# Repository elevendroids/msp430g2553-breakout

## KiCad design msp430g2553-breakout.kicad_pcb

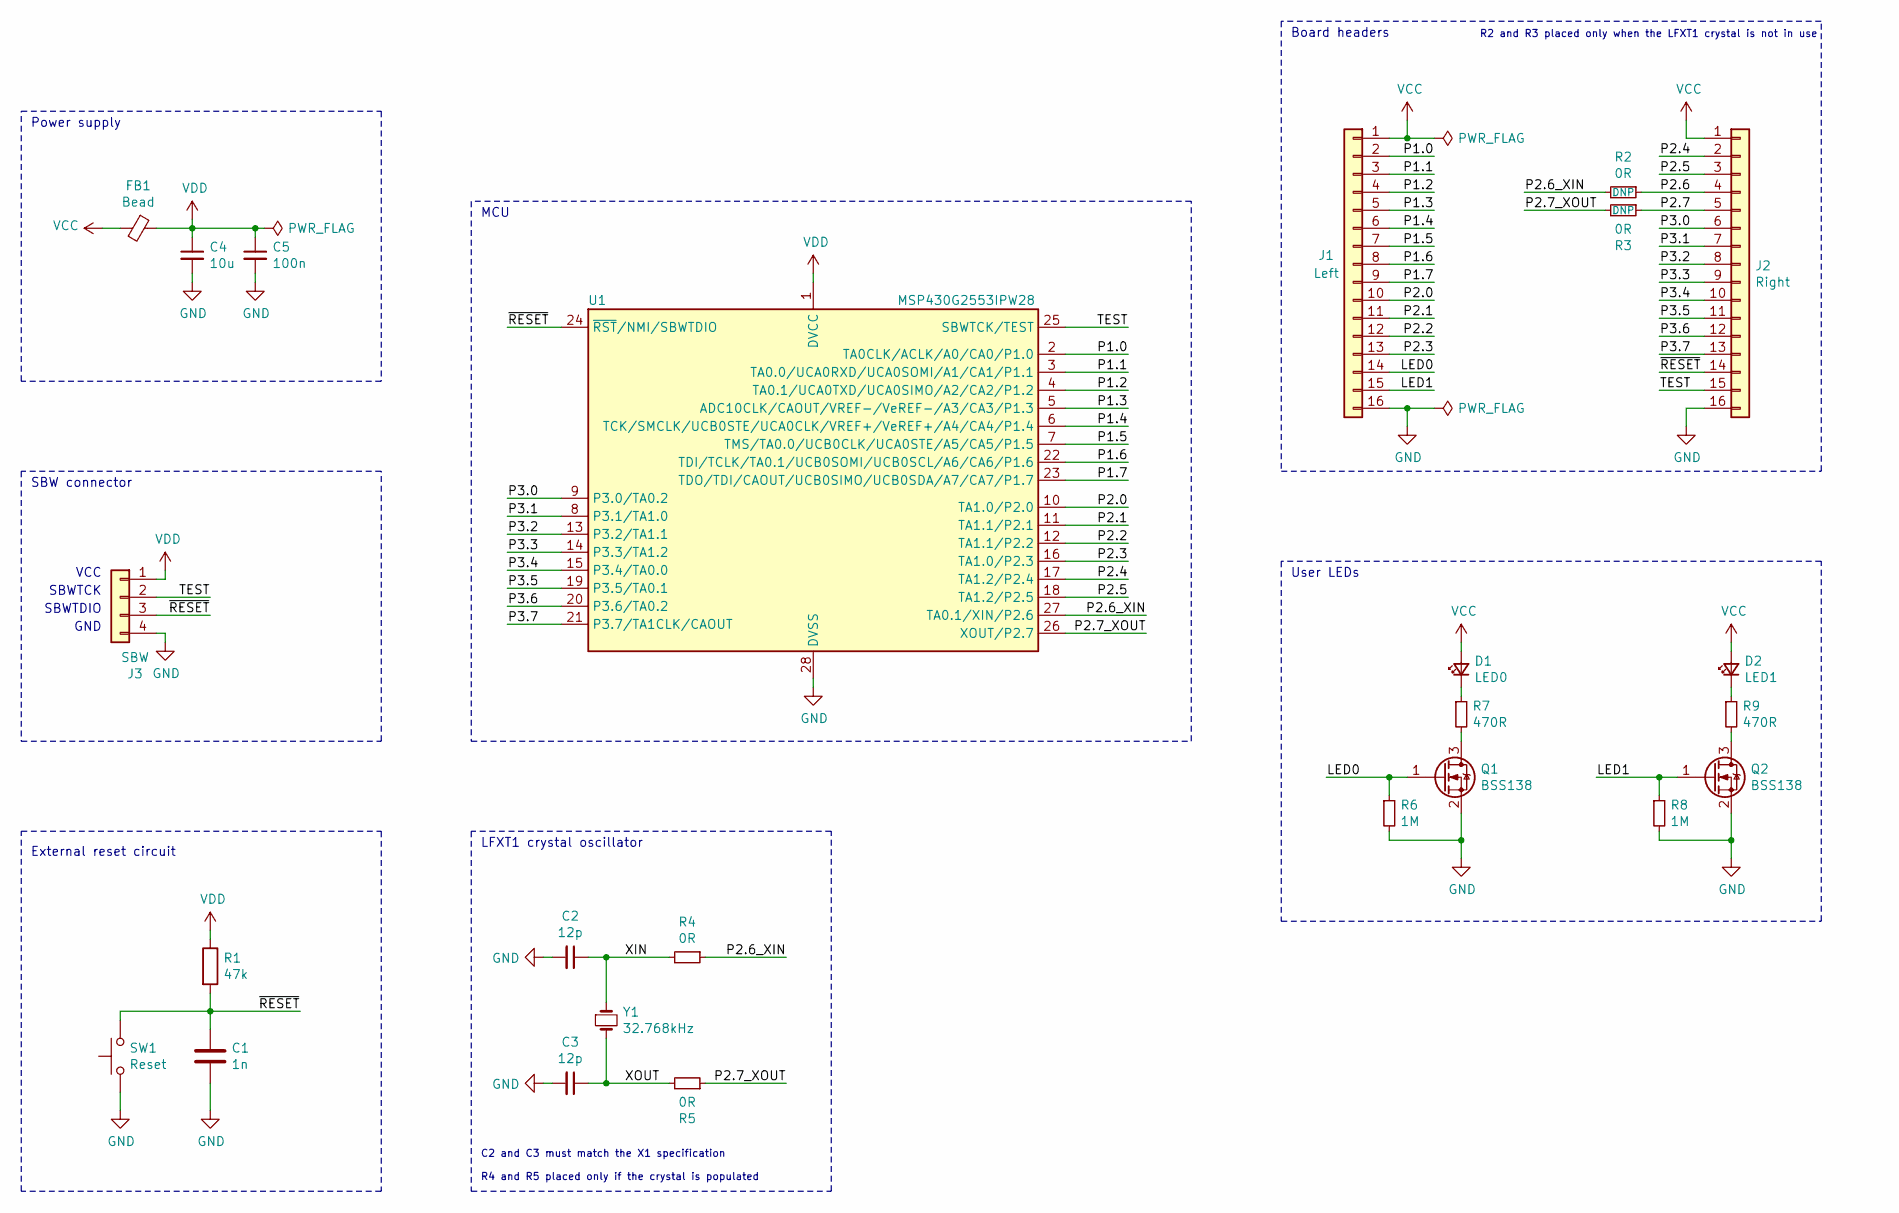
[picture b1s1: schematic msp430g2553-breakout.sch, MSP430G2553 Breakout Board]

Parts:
C1: 1n; C_0603_1608Metric
C2, C3: 12p; C_0603_1608Metric
C4: 10u; C_0805_2012Metric
C5: 100n; C_0603_1608Metric
D1: LED0; LED_0805_2012Metric
D2: LED1; LED_0805_2012Metric
FB1: Bead; L_0603_1608Metric
J1: Left; PinHeader_1x16_P2.54mm_Vertical
J2: Right; PinHeader_1x16_P2.54mm_Vertical
J3: SBW; PinHeader_1x04_P2.00mm_Vertical
Q1, Q2: BSS138; SOT-23
R1: 47k; R_0603_1608Metric
R2, R3, R4, R5: 0R; R_0402_1005Metric
R6, R8: 1M; R_0603_1608Metric
R7, R9: 470R; R_0603_1608Metric
SW1: Reset; SW_SPST_CK_RS282G05A3
U1: MSP430G2553IPW28; TSSOP-28_4.4x9.7mm_P0.65mm
Y1: 32.768kHz; Crystal_SMD_3215-2Pin_3.2x1.5mm

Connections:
/LED0: J1.14, Q1.1 (G), R6.1
/LED1: J1.15, Q2.1 (G), R8.1
/P1.0: J1.2, U1.2 (TA0CLK/ACLK/A0/CA0/P1.0)
/P1.1: J1.3, U1.3 (TA0.0/UCA0RXD/UCA0SOMI/A1/CA1/P1.1)
/P1.2: J1.4, U1.4 (TA0.1/UCA0TXD/UCA0SIMO/A2/CA2/P1.2)
/P1.3: J1.5, U1.5 (ADC10CLK/CAOUT/VREF-/VeREF-/A3/CA3/P1.3)
/P1.4: J1.6, U1.6 (TCK/SMCLK/UCB0STE/UCA0CLK/VREF+/VeREF+/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)
/P1.5: J1.7, U1.7 (TMS/TA0.0/UCB0CLK/UCA0STE/A5/CA5/P1.5)
/P1.6: J1.8, U1.22 (TDI/TCLK/TA0.1/UCB0SOMI/UCB0SCL/A6/CA6/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)
/P1.7: J1.9, U1.23 (TDO/TDI/CAOUT/UCB0SIMO/UCB0SDA/A7/CA7/P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)
/P2.0: J1.10, U1.10 (TA1.0/P2.0)
/P2.1: J1.11, U1.11 (TA1.1/P2.1)
/P2.2: J1.12, U1.12 (TA1.1/P2.2)
/P2.3: J1.13, U1.16 (TA1.0/P2.3)
/P2.4: J2.2, U1.17 (TA1.2/P2.4)
/P2.5: J2.3, U1.18 (TA1.2/P2.5)
/P2.6: J2.4, R2.1
/P2.6_XIN: R2.2, R4.1, U1.27 (TA0.1/XIN/P2.6)
/P2.7: J2.5, R3.1
/P2.7_XOUT: R3.2, R5.1, U1.26 (XOUT/P2.7)
/P3.0: J2.6, U1.9 (P3.0/TA0.2)
/P3.1: J2.7, U1.8 (P3.1/TA1.0)
/P3.2: J2.8, U1.13 (P3.2/TA1.1)
/P3.3: J2.9, U1.14 (P3.3/TA1.2)
/P3.4: J2.10, U1.15 (P3.4/TA0.0)
/P3.5: J2.11, U1.19 (P3.5/TA0.1)
/P3.6: J2.12, U1.20 (P3.6/TA0.2)
/P3.7: J2.13, U1.21 (P3.7/TA1CLK/CAOUT)
/TEST: J2.15, J3.2, U1.25 (SBWTCK/TEST)
/XIN: C2.1, R4.2, Y1.1
/XOUT: C3.1, R5.2, Y1.2
/~RESET: C1.1, J2.14, J3.3, R1.2, SW1.2, U1.24 (~RST~/NMI/SBWTDIO)
GND: C1.2, C2.2, C3.2, C4.2, C5.2, J1.16, J2.16, J3.4, Q1.2 (S), Q2.2 (S), R6.2, R8.2, SW1.1, U1.28 (DVSS)
unnamed: D1.1 (K), R7.1
unnamed: D2.1 (K), R9.1
unnamed: Q1.3 (D), R7.2
unnamed: Q2.3 (D), R9.2
VCC: D1.2 (A), D2.2 (A), FB1.2, J1.1, J2.1
VDD: C4.1, C5.1, FB1.1, J3.1, R1.1, U1.1 (DVCC)

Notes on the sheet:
External reset circuit
User LEDs
Power supply
SBW connector
MCU
Board headers
LFXT1 crystal oscillator
C2 and C3 must match the X1 specification R4 and R5 placed only if the crystal is populated
R2 and R3 placed only when the LFXT1 crystal is not in use
SBWTCK
SBWTDIO
VCC
GND

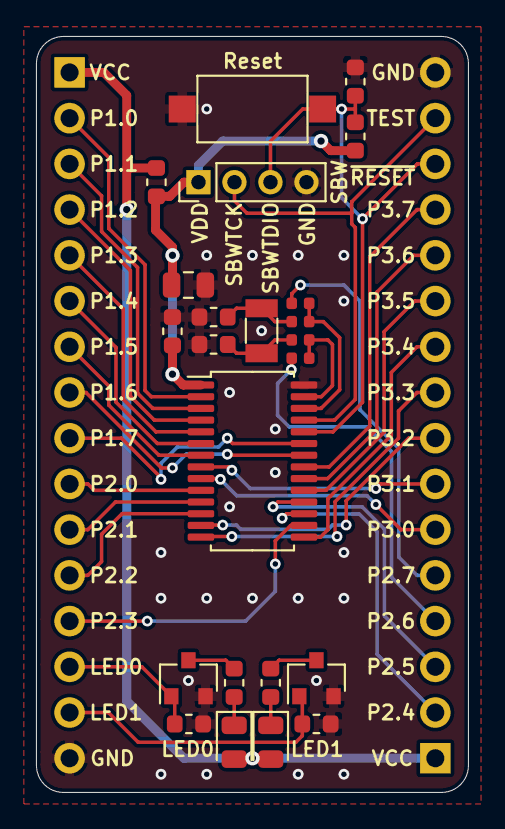
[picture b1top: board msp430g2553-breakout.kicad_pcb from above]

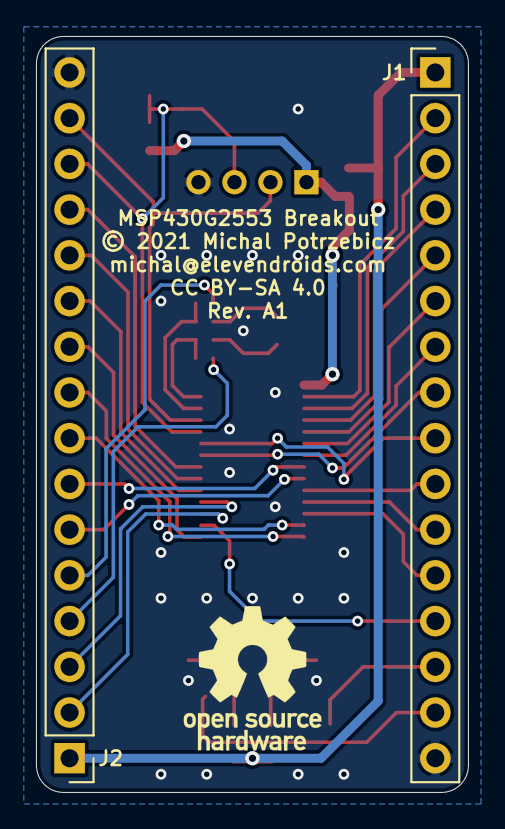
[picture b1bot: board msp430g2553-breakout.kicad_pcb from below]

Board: 2 copper layers, 24.0 x 42.0 mm, 25 parts (2 on the bottom side), 39 nets.

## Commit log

2021-04-01 Fixed swapped SBWTDIO and SBWTCK pins, revision bump to A1

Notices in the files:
msp430g2553-breakout.kicad_pcb:
License: CC BY-SA 4.0
© 2021 Michal Potrzebicz
CC BY-SA 4.0
